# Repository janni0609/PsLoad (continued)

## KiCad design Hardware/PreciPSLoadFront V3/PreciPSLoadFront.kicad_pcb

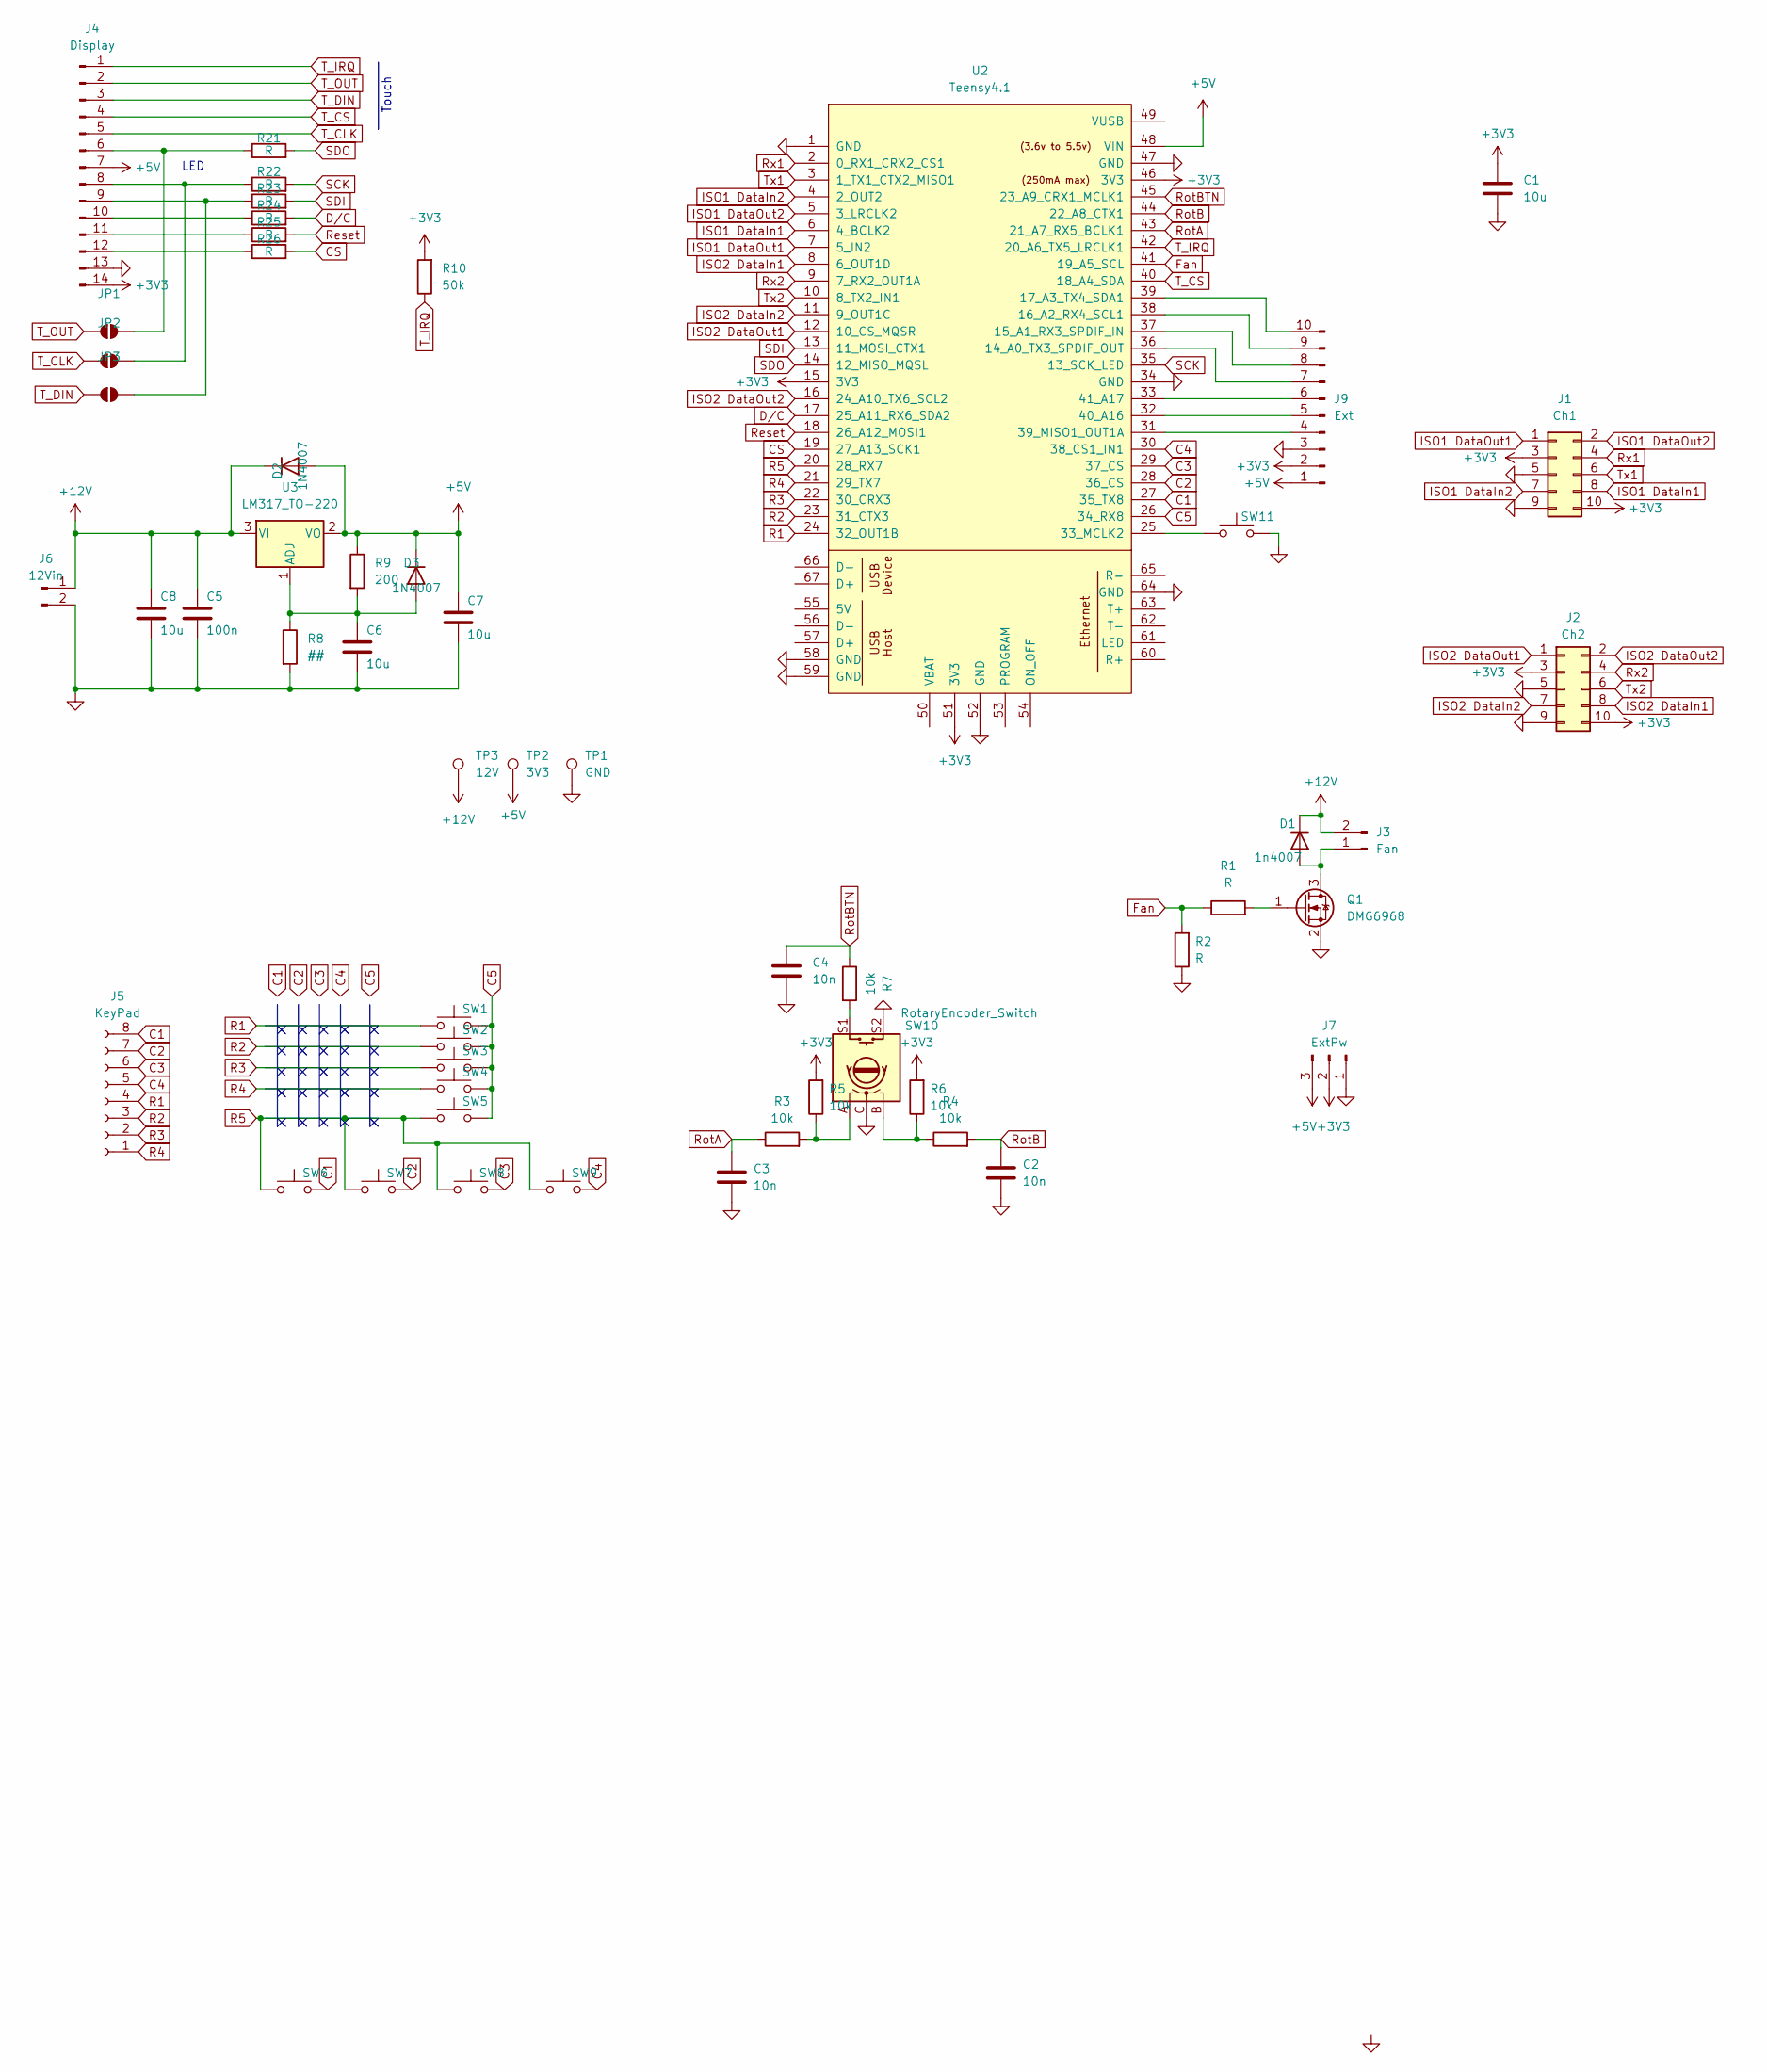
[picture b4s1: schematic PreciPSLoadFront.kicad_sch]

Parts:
C1, C6, C7, C8: 10u; C_1206_3216Metric
C2, C3, C4: 10n; C_0603_1608Metric
C5: 100n; C_1206_3216Metric
D1: 1n4007; D_SOD-123F
D2, D3: 1N4007; D_SOD-123F
J1: Ch1; IDC-Header_2x05_P2.54mm_Vertical
J2: Ch2; IDC-Header_2x05_P2.54mm_Vertical
J3: Fan; JST_XH_B2B-XH-A_1x02_P2.50mm_Vertical
J4: Display; PinSocket_1x14_P2.54mm_Vertical
J5: KeyPad; PinSocket_1x08_P2.54mm_Vertical
J6: 12Vin; JST_XH_B2B-XH-A_1x02_P2.50mm_Vertical
J7: ExtPw; JST_XH_B3B-XH-A_1x03_P2.50mm_Vertical
J9: Ext; PinHeader_1x10_P2.54mm_Vertical
JP1, JP2, JP3: SolderJumper_2_Open; SolderJumper-2_P1.3mm_Open_TrianglePad1.0x1.5mm
Q1: DMG6968; SOT-23-3
R1, R2, R21, R22, R23, R24, R25, R26: R; R_0603_1608Metric
R3, R4, R5, R6, R7: 10k; R_0603_1608Metric
R8: ##; R_0603_1608Metric
R9: 200; R_0603_1608Metric
R10: 50k; R_0603_1608Metric
SW1, SW2, SW3, SW4, SW5, SW6, SW7, SW8, SW9, SW11: SW_Push; Panel Push Btn
SW10: RotaryEncoder_Switch; RotaryEncoder_Bourns_Vertical_PEC12R-3x17F-Sxxxx
TP1: GND; SMD Test Point PCWCTE
TP2: 3V3; SMD Test Point PCWCTE
TP3: 12V; SMD Test Point PCWCTE
U2: Teensy4.1; Teensy41
U3: LM317_TO-220; TO-220-3_Vertical

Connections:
+3V3: C1.1, J1.3, J1.10, J2.3, J2.10, J4.14, J7.2, J9.2, R5.2, R6.2, R10.2, U2.15 (3V3), U2.46 (3V3), U2.51 (3V3)
+5V: C7.1, D2.2 (A), D3.1 (K), J4.7, J7.3, J9.1, R9.1, TP2.1, U2.48 (VIN), U3.2 (VO)
+12V: C5.1, C8.1, D1.1 (K), D2.1 (K), J3.2, J6.1, TP3.1, U3.3 (VI)
C1: J5.8, SW6.2, U2.27 (35_TX8)
C2: J5.7, SW7.2, U2.28 (36_CS)
C3: J5.6, SW8.2, U2.29 (37_CS)
C4: J5.5, SW9.2, U2.30 (38_CS1_IN1)
C5: SW1.2, SW2.2, SW3.2, SW4.2, SW5.2, U2.26 (34_RX8)
CS: R26.2, U2.19 (27_A13_SCK1)
D/C: R24.2, U2.17 (25_A11_RX6_SDA2)
Fan: R1.1, R2.2, U2.41 (19_A5_SCL)
GND: C1.2, C2.1, C3.1, C4.2, C5.2, C6.2, C7.2, C8.2, J1.5, J1.9, J2.5, J2.9, J4.13, J6.2, J7.1, J9.3, Q1.2 (S), R2.1, R8.2, SW10.C, SW10.S2, SW11.2, TP1.1, U2.1 (GND), U2.34 (GND), U2.47 (GND), U2.52 (GND), U2.58 (GND), U2.59 (GND), U2.64 (GND)
ISO1 DataIn1: J1.8, U2.6 (4_BCLK2)
ISO1 DataIn2: J1.7, U2.4 (2_OUT2)
ISO1 DataOut1: J1.1, U2.7 (5_IN2)
ISO1 DataOut2: J1.2, U2.5 (3_LRCLK2)
ISO2 DataIn1: J2.8, U2.8 (6_OUT1D)
ISO2 DataIn2: J2.7, U2.11 (9_OUT1C)
ISO2 DataOut1: J2.1, U2.12 (10_CS_MQSR)
ISO2 DataOut2: J2.2, U2.16 (24_A10_TX6_SCL2)
unnamed: D1.2 (A), J3.1, Q1.3 (D)
unnamed: C6.1, D3.2 (A), R8.1, R9.2, U3.1 (ADJ)
unnamed: J4.6, JP1.2 (B), R21.1
unnamed: J4.8, JP2.2 (B), R22.1
unnamed: J4.9, JP3.2 (B), R23.1
unnamed: J4.10, R24.1
unnamed: J4.11, R25.1
unnamed: J4.12, R26.1
unnamed: J9.4, U2.31 (39_MISO1_OUT1A)
unnamed: J9.5, U2.32 (40_A16)
unnamed: J9.6, U2.33 (41_A17)
unnamed: J9.7, U2.36 (14_A0_TX3_SPDIF_OUT)
unnamed: J9.8, U2.37 (15_A1_RX3_SPDIF_IN)
unnamed: J9.9, U2.38 (16_A2_RX4_SCL1)
unnamed: J9.10, U2.39 (17_A3_TX4_SDA1)
unnamed: Q1.1 (G), R1.2
unnamed: R3.2, R5.1, SW10.A
unnamed: R4.1, R6.1, SW10.B
unnamed: R7.2, SW10.S1
unnamed: SW11.1, U2.25 (33_MCLK2)
R1: J5.4, SW1.1, U2.24 (32_OUT1B)
R2: J5.3, SW2.1, U2.23 (31_CTX3)
R3: J5.2, SW3.1, U2.22 (30_CRX3)
R4: J5.1, SW4.1, U2.21 (29_TX7)
R5: SW5.1, SW6.1, SW7.1, SW8.1, SW9.1, U2.20 (28_RX7)
Reset: R25.2, U2.18 (26_A12_MOSI1)
RotA: C3.2, R3.1, U2.43 (21_A7_RX5_BCLK1)
RotB: C2.2, R4.2, U2.44 (22_A8_CTX1)
RotBTN: C4.1, R7.1, U2.45 (23_A9_CRX1_MCLK1)
Rx1: J1.4, U2.2 (0_RX1_CRX2_CS1)
Rx2: J2.4, U2.9 (7_RX2_OUT1A)
SCK: R22.2, U2.35 (13_SCK_LED)
SDI: R23.2, U2.13 (11_MOSI_CTX1)
SDO: R21.2, U2.14 (12_MISO_MQSL)
T_CLK: J4.5, JP2.1 (A)
T_CS: J4.4, U2.40 (18_A4_SDA)
T_DIN: J4.3, JP3.1 (A)
T_IRQ: J4.1, R10.1, U2.42 (20_A6_TX5_LRCLK1)
T_OUT: J4.2, JP1.1 (A)
Tx1: J1.6, U2.3 (1_TX1_CTX2_MISO1)
Tx2: J2.6, U2.10 (8_TX2_IN1)

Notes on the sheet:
Touch
LED

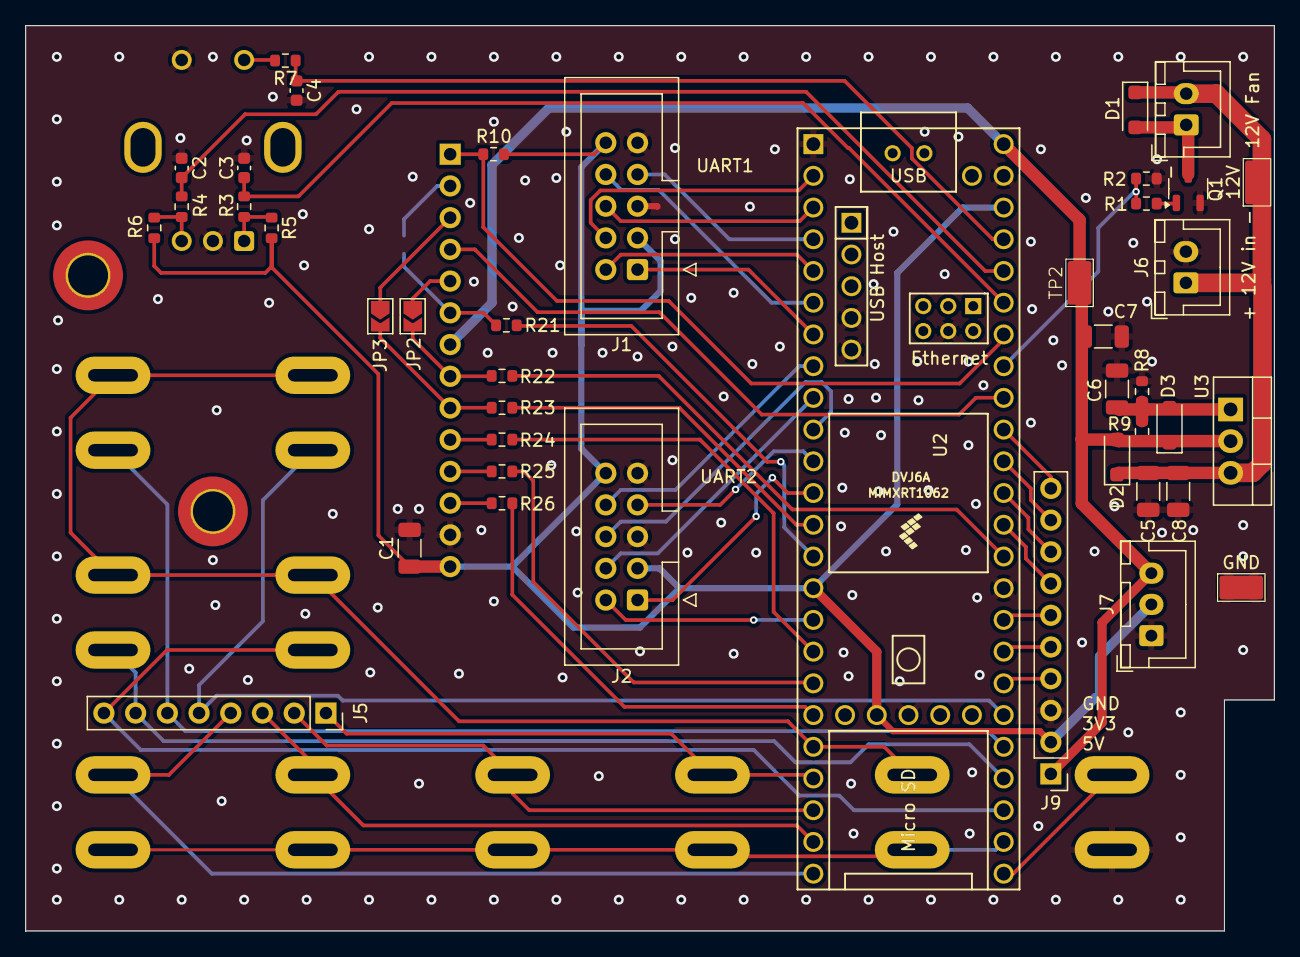
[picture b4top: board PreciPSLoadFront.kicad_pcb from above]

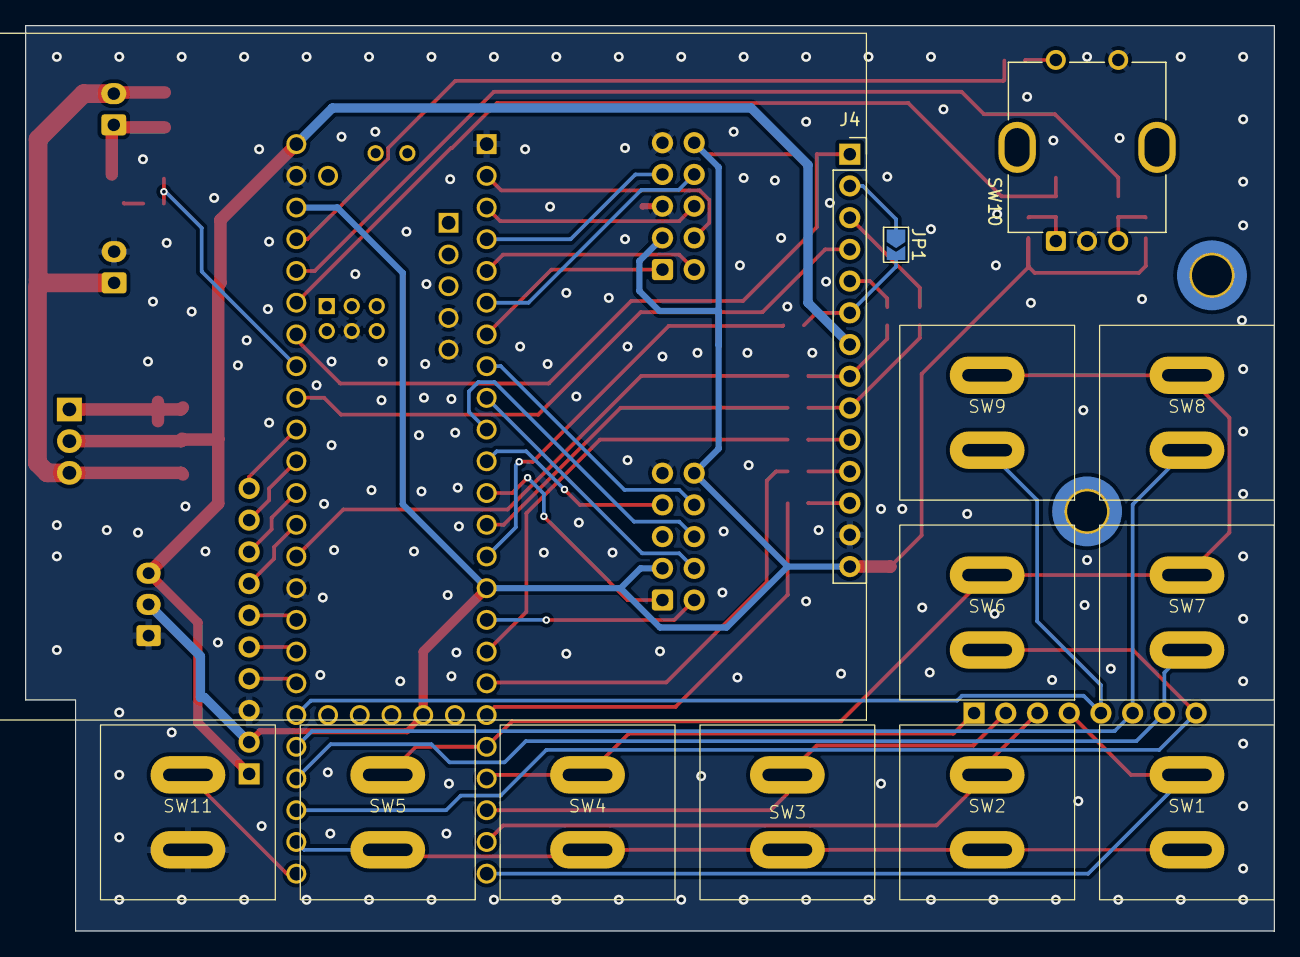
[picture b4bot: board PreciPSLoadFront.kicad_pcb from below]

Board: 2 copper layers, 100.0 x 72.5 mm, 55 parts (13 on the bottom side), 61 nets.

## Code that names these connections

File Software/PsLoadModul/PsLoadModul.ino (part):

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//DAC
#include <SPI.h>
#include <DAC7565.h>
DAC dac(PIN_PA5, PIN_PA7, PIN_PA4, PIN_PA1, PIN_PA3);

//++++++++++++++++++++++++++++++++++++++++++++++++++++++++++++++++++++++++++++++++++++++++++++++++++++
//ADC
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#include <SparkFun_ADS1219.h>
SfeADS1219ArdI2C myADC;
const uint8_t ADCReset = PIN_PC5;
//const uint8_t interruptPin = PIN_PC4;

//++++++++++++++++++++++++++++++++++++++++++++++++++++++++++++++++++++++++++++++++++++++++++++++++++++
//Timer Interrupt
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

//++++++++++++++++++++++++++++++++++++++++++++++++++++++++++++++++++++++++++++++++++++++++++++++++++++
const uint8_t SenseSW = PIN_PC3;
const uint8_t ON = PIN_PC0;
const uint8_t OnPhoto = PIN_PC1;

const uint8_t DataOut1 = PIN_PB4;       //Send Data
const uint8_t DataOut2 = PIN_PB5;       //Error flag

const uint8_t DataIn1 = PIN_PB6;
const uint8_t DataIn2 = PIN_PB7;

//++++++++++++++++++++++++++++++++++++++++++++++++++++++++++++++++++++++++++++++++++++++++++++++++++++
//Interpollation Cal
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  
//++++++++++++++++++++++++++++++++++++++++++++++++++++++++++++++++++++++++++++++++++++++++++++++++++++
//Temp
const uint8_t Temper1 = PIN_PC2;
const uint8_t Temper2 = PIN_PA2;

const uint8_t OTP = 60;           // Over temp Protection
bool OTP_flag = 0;
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  pinMode(OnPhoto, OUTPUT);
  digitalWrite(OnPhoto, LOW);

  pinMode(DataIn2, INPUT);
  pinMode(DataIn1, INPUT);
  attachInterrupt(digitalPinToInterrupt(DataIn1),  ReadData, FALLING);

  pinMode(DataOut1, OUTPUT);
  pinMode(DataOut2, OUTPUT);
  digitalWrite(DataOut1, HIGH);
  digitalWrite(DataOut2, LOW);
  
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
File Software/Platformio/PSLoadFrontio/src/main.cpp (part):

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
  uint32_t myTime;

  const uint8_t DataIn1 = 5;
  const uint8_t DataIn2 = 3;
  const uint8_t DataOut1 = 4;
  const uint8_t DataOut2 = 2;

  const uint8_t InterrSW = 33;

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
  const uint8_t Debug = 40;

  const uint8_t Fan = 19;

  bool Error = 0;

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  const uint8_t RotClk = 21;
  const uint8_t RotDt = 22;

  const uint8_t RotBtn = 13;

  bool last_run = LOW;
  bool aState;
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  //Encoder
  pinMode(RotClk, INPUT);
  pinMode(RotDt, INPUT);
  pinMode(RotBtn, INPUT_PULLUP);

  attachInterrupt(digitalPinToInterrupt(RotBtn),  RotBtnISR, FALLING);
  attachInterrupt(digitalPinToInterrupt(RotClk),  shaft_moved, CHANGE);
  //------------------------------------------------------------------------------------------------

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  

  
  pinMode(DataOut1, OUTPUT);
  pinMode(DataOut2, OUTPUT);



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  digitalWrite(DataOut1, LOW);
  digitalWrite(DataOut2, LOW);

  pinMode(DataIn2, INPUT);
  attachInterrupt(DataIn2, ErrorCh1_ISR, RISING);

  pinMode(DataIn1, INPUT);
  attachInterrupt(DataIn1, DataReadyCH1, RISING);

  
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
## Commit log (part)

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2024-05-15 Cleanup
    remove Interpollation
2024-05-15 name change
2024-05-15 name change2
2024-05-15 datatyp const
2024-05-15 variable def
2024-05-15 cleanup and Over Temp Protection
2024-05-15 cleanup
2024-05-16 cal work
2024-05-17 buzzer
2024-05-17 command list
2024-05-17 Add ToDo List
2024-05-18 Cal fix?
2024-05-18 first oop test
2024-05-18 check every cycle
2024-05-18 update ToDo
2024-05-20 opp unordentlich
2024-05-20 opp working
2024-05-20 oop cleanup
2024-05-20 increas Bd rate
2024-05-20 recover cal code
2024-05-20 cal oop
2024-05-20 Front Pw dist PCB
2024-05-21 OVP Handel & first capacity meas
2024-05-21 todo
2024-05-21 test time for funct.
2024-05-21 rework checkKeys funct.
2024-05-21 OTP (working)
2024-05-22 PlatformIO Test
2024-05-22 PS Module Platform Io
2024-05-22 organize folder
2024-05-22 increase wire clock speed
2024-05-22 remove serial statements
2024-05-23 Front to platform io
2024-05-23 (fix) startup
2024-05-26 test sprit and ui
2024-05-27 tweek ui
2024-05-29 time
2024-05-29 constrain with beep
2024-05-29 test capasity mes.
2024-05-30 improove data Rx funct.
2024-06-07 temp
2024-06-08 update Hardware
    Mosfet Fb and R
    Change -12V Supply
2024-06-12 hardware show
2024-06-13 hardware stuff
2024-06-13 add hardware 2_1
2024-06-13 update to list
2024-06-16 improove gnd
2024-06-17 work hardware
2024-06-17 hardware
2024-06-18 hardware work
2024-06-19 hardware work ##
2024-06-20 hardware relay
2024-06-22 range switch
2024-06-23 hardware Fet Range switching
2024-06-23 rooting and new frontDist
2024-06-24 finalise rooting
2024-07-02 hardware ####
2025-02-07 new revision
2025-02-11 heatsink
2025-05-31 .
    .
2025-06-20 new front dist and updates
2026-05-31 folder cleanup and removed hardware
2026-05-31 add costum workspace
2026-06-01 big fixes
2026-06-10 change todo
